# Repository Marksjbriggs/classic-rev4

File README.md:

# Information

This is the design for the Classic Rev4 Nixie Clock Module

Copyright 2015-2019 Ian Sparkes

This board is published under Creative Commons CC-BY-SA

We ask for modifications and contributions to be submitted to

nixie at protonmail.com

# code

The code is available here:

https://bitbucket.org/isparkes/nixiefirmwarev1/src/master/

4 Digit code is in the directory: ardunixFade9_4_digit

6 Digit code is in the directory: ardunixFade9_6_digit

# Support

You can get support for this board at

https://www.nixieclock.biz under the "Support" section.

If you bought the board from us, support is free. If you made it yourself or bought it from someone else, we ask a support fee of $10.

# Purchase

You can get ready made PCBs and kits from 

https://www.nixieclock.biz/StoreClassic.html

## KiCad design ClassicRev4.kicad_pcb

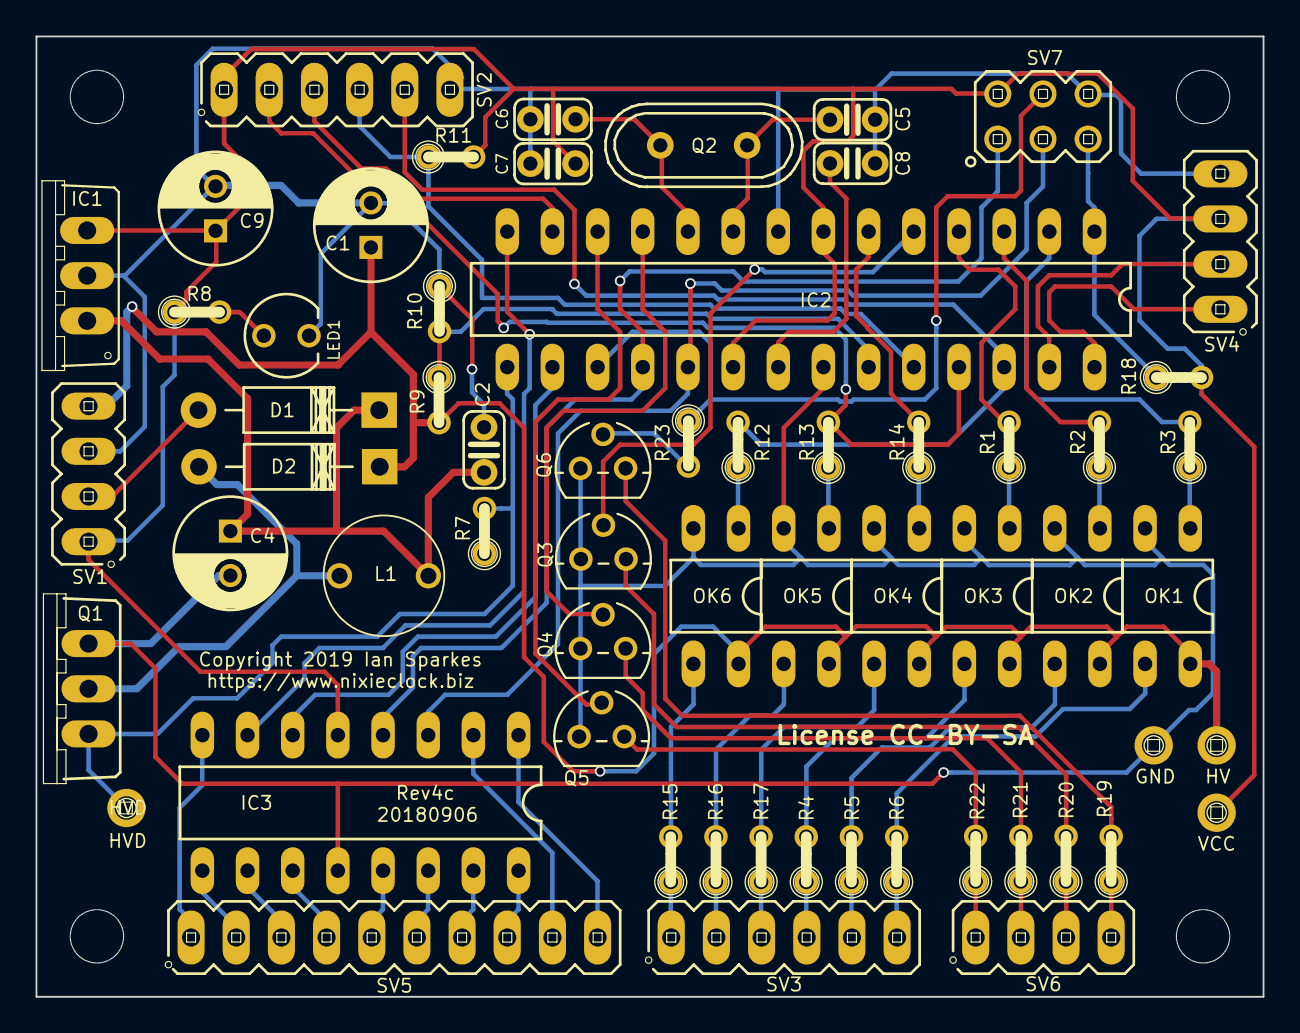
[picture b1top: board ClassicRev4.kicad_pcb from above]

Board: 2 copper layers, 69.0 x 54.0 mm, 65 parts (0 on the bottom side), 68 nets.

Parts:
C1: 2.2uF; C_Radial_D6.3_L11.2_P2.5
C2, C7, C8: 100nF; C025-024X044
C4, C9: 220uF; C_Radial_D6.3_L11.2_P2.5
C5, C6: 22pF; C025-024X044
D1: 1N4001; Diode_DO-41_1N4001
D2: UF4007; Diode_DO-41_1N4001
IC1: 7805TV; 7805_TO220V
IC2: MEGA8-P; 328P_DIL28
IC3: K155ID1; 74141_DIL16
L1: 100uH; Inductor-100mH
LED1: Power; LED_3MM
MH1, MH2, MH3, MH4: MountingHole_3mm
OK1, OK2, OK3, OK4, OK5, OK6: EL817C; optocoupler-DIL04
Q1: IRF740; TRANSISTOR-POWER_TO220BV
Q2: 16MHz; Crystal_HC49-U_Vertical
Q3, Q4, Q5, Q6: 2N7000; 2N7000_TO92
R1, R2, R3, R12, R13, R14, R19, R20, R21, R22, R23: 1k; R-0207_2V
R4, R5, R6, R7, R8, R15, R16, R17: 2.7k; R-0207_2V
R9: 390k; R-0207_2V
R10: 4.7k; R-0207_2V
R11, R18: 10k; R-0207_2V
SV1: PWR; Header_MA04-1
SV2: CONN_FRONT; Header_MA06-1
SV3: CONN_01X06; Header_MA06-1
SV4: CONN_RTC; Header_MA04-1
SV5: CONN_01X10; Header_MA10-1
SV6: CONN_LED; Header_MA04-1
SV7: CONN_ISCP; Header_MA03-2
TP1: HV; TESTPAD_P1-13
TP2: GND; TESTPAD_P1-13
TP3: VCC; TESTPAD_P1-13
TP4: HVD; TESTPAD_P1-13

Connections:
/170V: C1.1, D2.1, OK1.4, OK2.4, OK3.4, OK4.4, OK5.4, OK6.4, R9.2, SV1.4, TP1.1
/ANODE1: IC2.2, R3.2
/ANODE2: IC2.3, R2.2
/ANODE3: IC2.4, R1.2
/ANODE4: IC2.6, R14.2
/ANODE5: IC2.25, R13.2, SV2.2
/ANODE6: IC2.26, R12.2, SV2.5
/AREF: C8.2, IC2.21
/BTN1: IC2.13, SV2.3
/B_GATE: IC2.5, Q3.2
/B_LED: R20.1, SV6.3
/CATHODE_0: IC3.8, SV5.1
/CATHODE_1: IC3.9, SV5.2
/CATHODE_2: IC3.10, SV5.3
/CATHODE_3: IC3.11, SV5.4
/CATHODE_4: IC3.13, SV5.5
/CATHODE_5: IC3.14, SV5.6
/CATHODE_6: IC3.15, SV5.7
/CATHODE_7: IC3.16, SV5.8
/CATHODE_8: IC3.2, SV5.9
/CATHODE_9: IC3.1, SV5.10
/DIGIT_A: IC2.19, IC3.3, SV7.3
/DIGIT_B: IC2.16, IC3.6
/DIGIT_C: IC2.14, IC3.7
/DIGIT_D: IC2.18, IC3.4, SV7.1
/DLS: IC2.24, R11.1, SV2.4
/DRAIN: D2.2, L1.1, Q1.D
/G_GATE: IC2.11, Q4.2
/G_LED: R21.1, SV6.2
/HVD: IC2.15, Q1.G, R7.2, TP4.1
/HVS: IC2.23, R9.1, R10.2
/MOSI: IC2.17, R23.1, SV7.4
/RESET: IC2.1, R18.1, SV7.5
/R_GATE: IC2.12, Q5.2
/R_LED: R22.1, SV6.1
/SCL: IC2.28, SV4.1
/SDA: IC2.27, SV4.2
/TICK_BASE: Q6.2, R23.2
/TICK_LED: R19.1, SV6.4
/VCC: C7.1, C9.1, IC1.3, IC2.7, IC2.20, IC3.5, R8.1, R11.2, R18.2, SV1.1, SV2.1, SV4.3, SV7.2, TP3.1
/VIN: C2.2, C4.1, D1.1, IC1.1, L1.2
/XTAL1: C5.2, IC2.9, Q2.2
/XTAL2: C6.1, IC2.10, Q2.1
GND: C1.2, C2.1, C4.2, C5.1, C6.2, C7.2, C8.1, C9.2, IC1.2, IC2.8, IC2.22, IC3.12, LED1.K, OK1.2, OK2.2, OK3.2, OK4.2, OK5.2, OK6.2, Q1.S, Q3.3, Q4.3, Q5.3, Q6.3, R7.1, R10.1, SV1.3, SV2.6, SV4.4, SV7.6, TP2.1
unnamed: D1.2, SV1.2
unnamed: LED1.A, R8.2
unnamed: OK1.1, R3.1
unnamed: OK1.3, R6.2
unnamed: OK2.1, R2.1
unnamed: OK2.3, R5.2
unnamed: OK3.1, R1.1
unnamed: OK3.3, R4.2
unnamed: OK4.1, R14.1
unnamed: OK4.3, R17.2
unnamed: OK5.1, R13.1
unnamed: OK5.3, R16.2
unnamed: OK6.1, R12.1
unnamed: OK6.3, R15.2
unnamed: Q3.1, R20.2
unnamed: Q4.1, R21.2
unnamed: Q5.1, R22.2
unnamed: Q6.1, R19.2
unnamed: R4.1, SV3.4
unnamed: R5.1, SV3.5
unnamed: R6.1, SV3.6
unnamed: R15.1, SV3.1
unnamed: R16.1, SV3.2
unnamed: R17.1, SV3.3

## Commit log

2018-10-14 Initial version Classic Rev4b
2018-10-14 Initial commit Classic Rev4c
2018-10-25 Correct values and divide more logically
2019-01-18 KiCad 5
2019-11-12 Set voltage
2019-11-12 Set license
2019-11-15 Add copyright and license notices
2019-11-15 Add link for the store
2019-11-15 Add link to code

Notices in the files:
ClassicRev4.kicad_pcb:
License CC-BY-SA
Copyright 2019 Ian Sparkes
